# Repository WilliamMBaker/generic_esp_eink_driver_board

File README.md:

# generic_esp_eink_driver_board

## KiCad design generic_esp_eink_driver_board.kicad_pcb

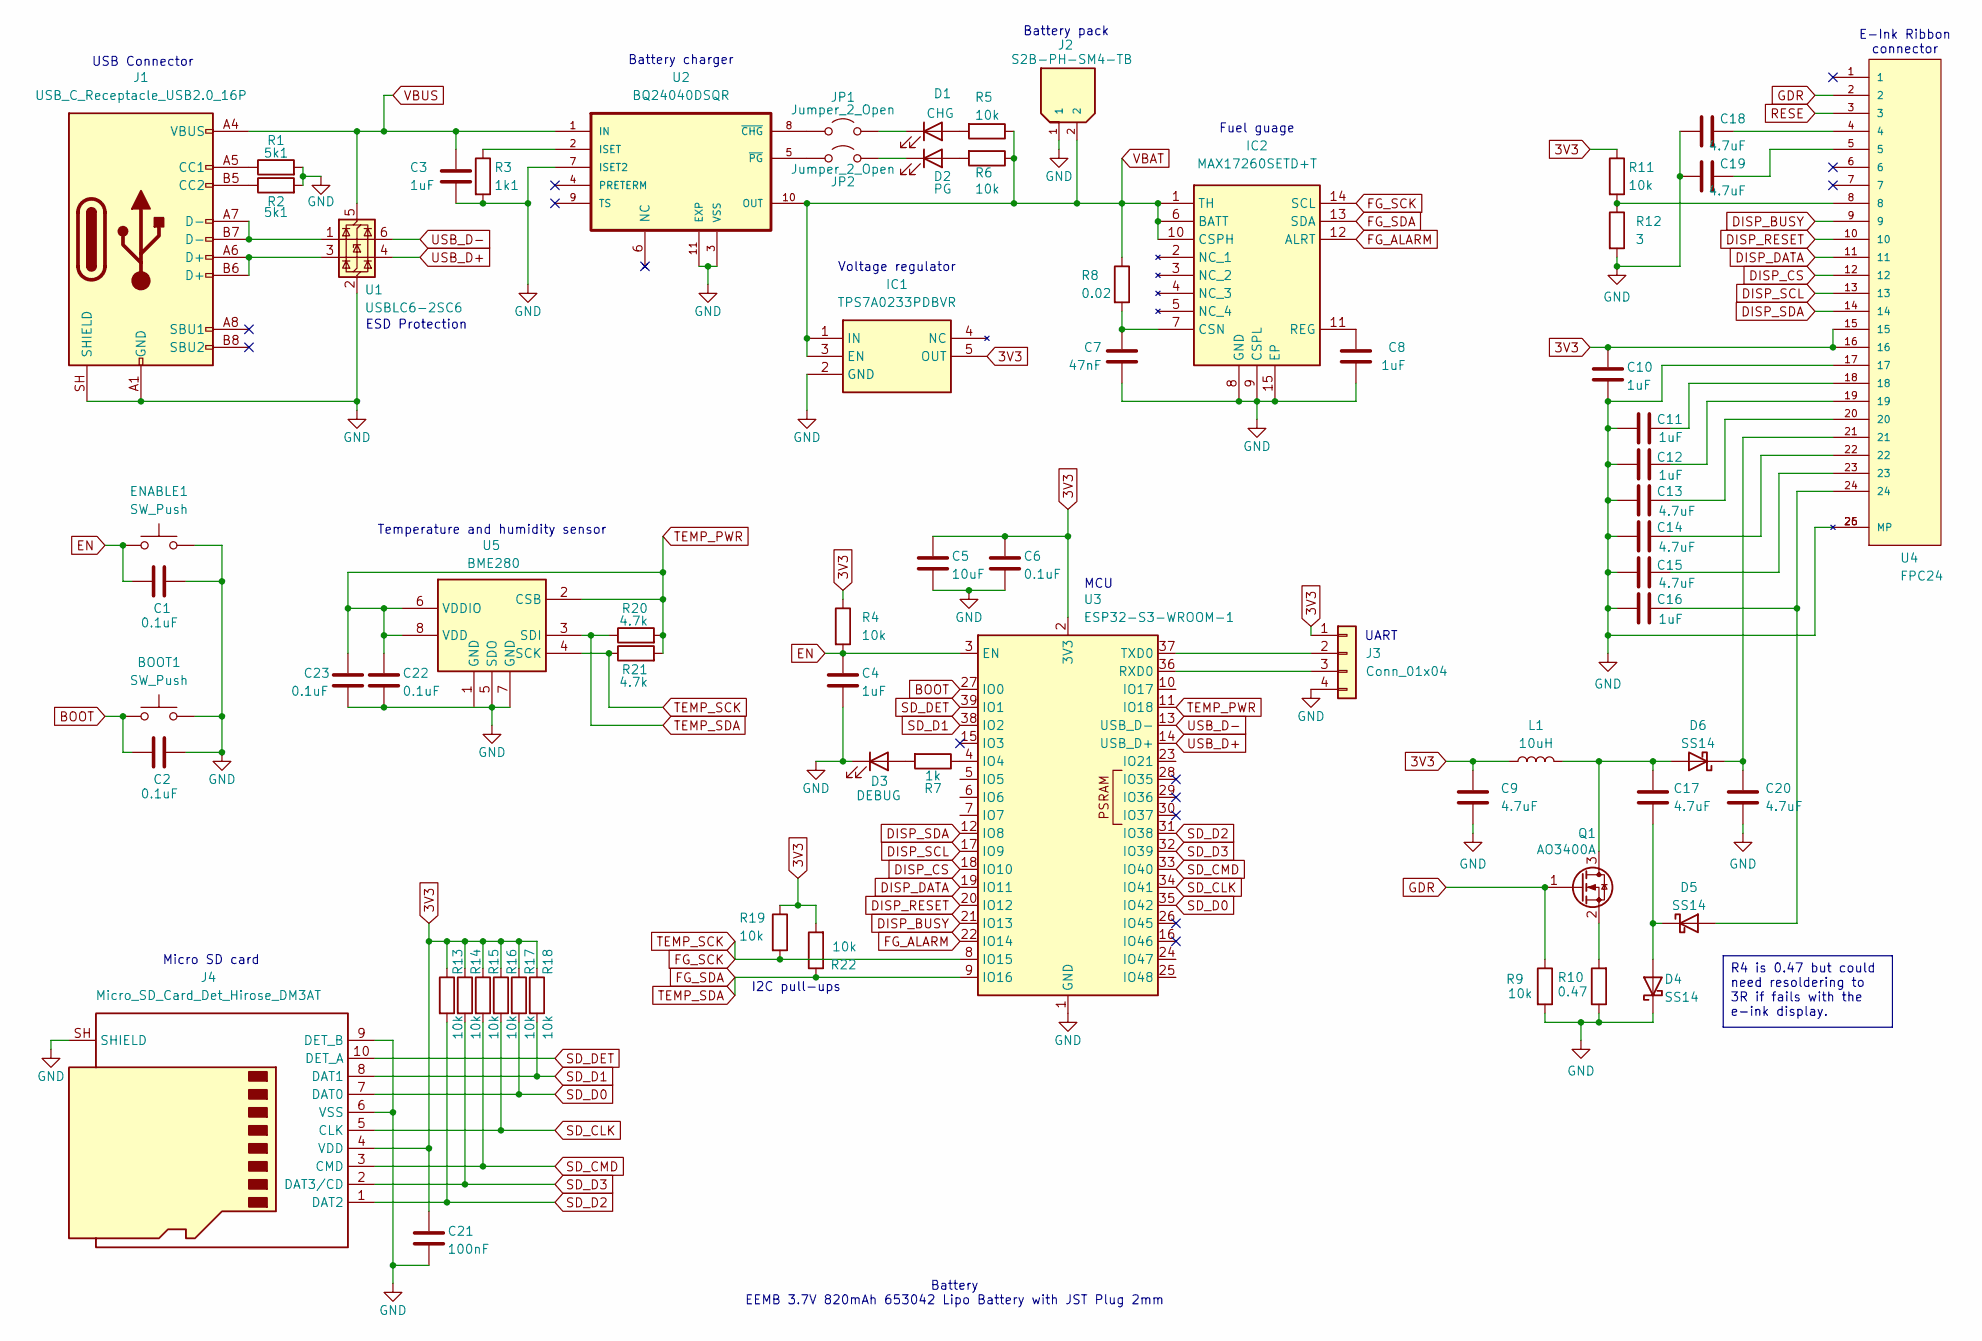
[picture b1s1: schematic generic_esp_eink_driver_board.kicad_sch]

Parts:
BOOT1: SW_Push; SW_Push_1P1T_XKB_TS-1187A
C1, C2, C6, C22, C23: 0.1uF; C_0805_2012Metric_Pad1.18x1.45mm_HandSolder
C3, C4, C8, C10, C11, C12, C16: 1uF; C_0805_2012Metric_Pad1.18x1.45mm_HandSolder
C5: 10uF; C_0805_2012Metric_Pad1.18x1.45mm_HandSolder
C7: 47nF; C_0805_2012Metric_Pad1.18x1.45mm_HandSolder
C9, C13, C14, C15, C17, C18, C19, C20: 4.7uF; C_0805_2012Metric_Pad1.18x1.45mm_HandSolder
C21: 100nF; C_0805_2012Metric_Pad1.18x1.45mm_HandSolder
D1: CHG; LED_0805_2012Metric
D2: PG; LED_0805_2012Metric
D3: DEBUG; LED_0805_2012Metric
D4, D5, D6: SS14; D_SMA
ENABLE1: SW_Push; SW_Push_1P1T_XKB_TS-1187A
IC1: TPS7A0233PDBVR; SOT95P280X145-5N; Manufacturer_Part_Number TPS7A0233PDBVR; Mouser Part Number 595-TPS7A0233PDBVR
IC2: MAX17260SETD+T; SON40P300X300X80-15N; Manufacturer_Part_Number MAX17260SETD+T; Mouser Part Number 700-MAX17260SETD+T
J1: USB_C_Receptacle_USB2.0_16P; USB_C_Receptacle_GCT_USB4105-xx-A_16P_TopMnt_Horizontal
J2: S2B-PH-SM4-TB; JST_PH_S2B-PH-SM4-TB_1x02-1MP_P2.00mm_Horizontal; PARTREV N/A
J3: Conn_01x04; PinHeader_1x04_P2.54mm_Vertical
J4: Micro_SD_Card_Det_Hirose_DM3AT; microSD_HC_Hirose_DM3AT-SF-PEJM5
JP1, JP2: Jumper_2_Open; SolderJumper-2_P1.3mm_Open_TrianglePad1.0x1.5mm
L1: 10uH; L_0805_2012Metric_Pad1.05x1.20mm_HandSolder
Q1: AO3400A; SOT-23
R1, R2: 5k1; R_0805_2012Metric_Pad1.20x1.40mm_HandSolder
R3: 1k1; R_0805_2012Metric_Pad1.20x1.40mm_HandSolder
R4, R5, R6, R9, R11, R13, R14, R15, R16, R17, R18, R19, R22: 10k; R_0805_2012Metric_Pad1.20x1.40mm_HandSolder
R7: 1k; R_0805_2012Metric_Pad1.20x1.40mm_HandSolder
R8: 0.02; R_0805_2012Metric_Pad1.20x1.40mm_HandSolder
R10: 0.47; R_0805_2012Metric_Pad1.20x1.40mm_HandSolder
R12: 3; R_0805_2012Metric_Pad1.20x1.40mm_HandSolder
R20, R21: 4.7k; R_0805_2012Metric_Pad1.20x1.40mm_HandSolder
U1: USBLC6-2SC6; SOT-23-6
U2: BQ24040DSQR; SON40P200X200X80-11N
U3: ESP32-S3-WROOM-1
U4: FPC24; CONN24X1_CF35242D0RE-NH_CVI
U5: BME280; Bosch_LGA-8_2.5x2.5mm_P0.65mm_ClockwisePinNumbering

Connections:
3V3: C5.1, C6.1, C9.1, C10.1, C21.1, IC1.5 (OUT), J3.1, J4.4 (VDD), L1.1, R4.1, R11.1, R13.1, R14.1, R15.1, R16.1, R17.1, R18.1, R19.1, R22.2, U3.2 (3V3), U4.15, U4.16
BOOT: BOOT1.1, C2.1, U3.27 (IO0)
DISP_BUSY: U3.21 (IO13), U4.9
DISP_CS: U3.18 (IO10), U4.12
DISP_DATA: U3.19 (IO11), U4.11
DISP_RESET: U3.20 (IO12), U4.10
DISP_SCL: U3.17 (IO9), U4.13
DISP_SDA: U3.12 (IO8), U4.14
EN: C1.1, C4.1, ENABLE1.1, R4.2, U3.3 (EN)
FG_ALARM: IC2.12 (ALRT), U3.22 (IO14)
FG_SCK: IC2.14 (SCL), R19.2, R21.1, U3.8 (IO15), U5.4 (SCK)
FG_SDA: IC2.13 (SDA), R20.1, R22.1, U3.9 (IO16), U5.3 (SDI)
GDR: Q1.1 (G), R9.1, U4.2
GND: BOOT1.2, C1.2, C2.2, C3.2, C4.2, C5.2, C6.2, C7.2, C8.2, C9.2, C10.2, C11.1, C12.1, C13.1, C14.1, C15.1, C16.1, C18.1, C19.1, C20.2, C21.2, C22.2, C23.2, D3.1 (K), D4.1 (K), ENABLE1.2, IC1.2 (GND), IC2.8 (GND), IC2.9 (CSPL), IC2.15 (EP), J1.A1 (GND), J1.A12 (GND), J1.B1 (GND), J1.B12 (GND), J1.SH (SHIELD), J2.1, J3.4, J4.6 (VSS), J4.9 (DET_B), J4.SH (SHIELD), R1.2, R2.2, R3.2, R9.2, R10.1, R12.2, U1.2 (GND), U2.3 (VSS), U2.7 (ISET2), U2.11 (EXP), U3.1 (GND), U3.40 (GND), U3.41 (GND), U4.17, U4.25 (MP), U4.26 (MP), U5.5 (SDO), U5.7 (GND)
unnamed: C11.2, U4.18
unnamed: C12.2, U4.19
unnamed: C13.2, U4.20
unnamed: C14.2, U4.22
unnamed: C15.2, U4.23
unnamed: C18.2, U4.4
unnamed: C19.2, U4.5
unnamed: D1.2 (A), R5.2
unnamed: D1.1 (K), JP1.2 (B)
unnamed: D2.2 (A), R6.2
unnamed: D2.1 (K), JP2.2 (B)
unnamed: D3.2 (A), R7.2
unnamed: C17.2, D4.2 (A), D5.1 (K)
unnamed: C16.2, D5.2 (A), U4.24
unnamed: C17.1, D6.2 (A), L1.2, Q1.3 (D)
unnamed: C20.1, D6.1 (K), U4.21
unnamed: C7.1, IC2.7 (CSN), R8.2
unnamed: C8.1, IC2.11 (REG)
unnamed: J1.A5 (CC1), R1.1
unnamed: J1.B5 (CC2), R2.1
unnamed: J1.A6 (D+), J1.B6 (D+), U1.3 (I/O2)
unnamed: J1.A7 (D-), J1.B7 (D-), U1.1 (I/O1)
unnamed: J3.2, U3.37 (TXD0)
unnamed: J3.3, U3.36 (RXD0)
unnamed: JP1.1 (A), U2.8 (~CHG)
unnamed: JP2.1 (A), U2.5 (~PG)
unnamed: Q1.2 (S), R10.2
unnamed: R11.2, R12.1, U4.8
unnamed: R3.1, U2.2 (ISET)
unnamed: R7.1, U3.4 (IO4)
RESE: U4.3
SD_CLK: J4.5 (CLK), R16.2, U3.34 (IO41)
SD_CMD: J4.3 (CMD), R15.2, U3.33 (IO40)
SD_D0: J4.7 (DAT0), R17.2, U3.35 (IO42)
SD_D1: J4.8 (DAT1), R18.2, U3.38 (IO2)
SD_D2: J4.1 (DAT2), R13.2, U3.31 (IO38)
SD_D3: J4.2 (DAT3/CD), R14.2, U3.32 (IO39)
SD_DET: J4.10 (DET_A), U3.39 (IO1)
TEMP_PWR: C22.1, C23.1, R20.2, R21.2, U3.11 (IO18), U5.2 (CSB), U5.6 (VDDIO), U5.8 (VDD)
USB_D+: U1.4 (I/O2), U3.14 (USB_D+)
USB_D-: U1.6 (I/O1), U3.13 (USB_D-)
VBAT: IC1.1 (IN), IC1.3 (EN), IC2.1 (TH), IC2.6 (BATT), IC2.10 (CSPH), J2.2, R5.1, R6.1, R8.1, U2.10 (OUT)
VBUS: C3.1, J1.A4 (VBUS), J1.A9 (VBUS), J1.B4 (VBUS), J1.B9 (VBUS), U1.5 (VBUS), U2.1 (IN)

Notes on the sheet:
Fuel guage
Temperature and humidity sensor
ESD Protection
Voltage regulator
I2C pull-ups
USB Connector
Micro SD card
E-Ink Ribbon connector
UART
MCU
Battery charger
Battery pack
Battery EEMB 3.7V 820mAh 653042 Lipo Battery with JST Plug 2mm
R4 is 0.47 but could need resoldering to 3R if fails with the e-ink display.

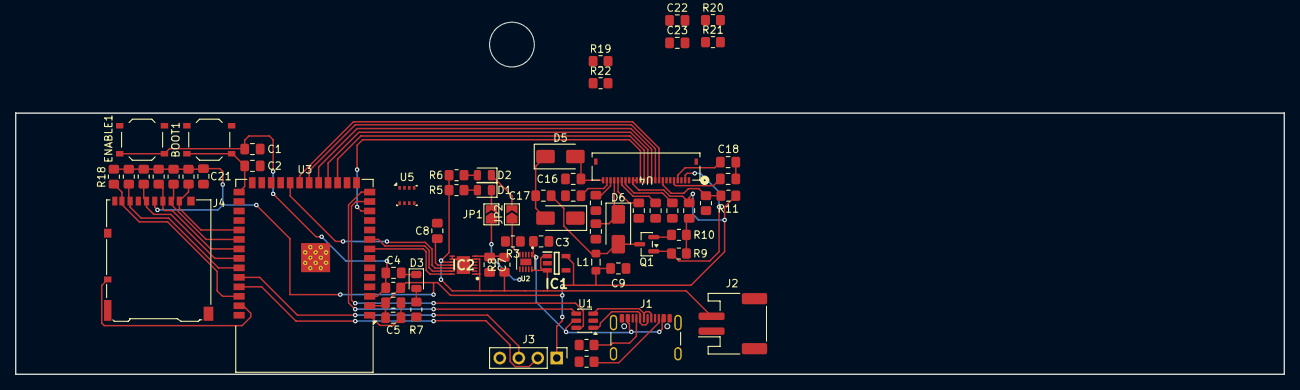
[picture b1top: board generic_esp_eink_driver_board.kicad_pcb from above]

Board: 2 copper layers, 170.0 x 35.0 mm, 68 parts (0 on the bottom side), 56 nets.
